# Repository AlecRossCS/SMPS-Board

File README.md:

# SMPS-Board
This is a Switch Mode Power Supply Board based on the LM2576, with output capibilities of 3.3-36V, 3A. 

### Design
this is designed to be an independent board to be the main power supply for most projects, it does not take mains input, input is meant to be either plugpack, or independent AC-DC Unit such as a Meanwell 24v, 300W supply and then transform it into 3.3V, 5V, or 12V. 

this design uses the multifaceted nature of the LM2576, as it will work with the LM2576-ADJ, LM2576-HV, LM2576-F3.3, LM2576-F5, or LM2576-F12. This meant some concern had to be taken to allow it to work either with the Adjustable or fixed versions. Some of the design rules are taken from the APP notes of the TI version datasheet. it is also designed with input protection of a PMOSFET (rather than diode protection).
It is designed to take full use of all of the copper surface of the PCB, as all of the copper is paid for to produce anyway with large planes to carry current as well as heat.

mockup:

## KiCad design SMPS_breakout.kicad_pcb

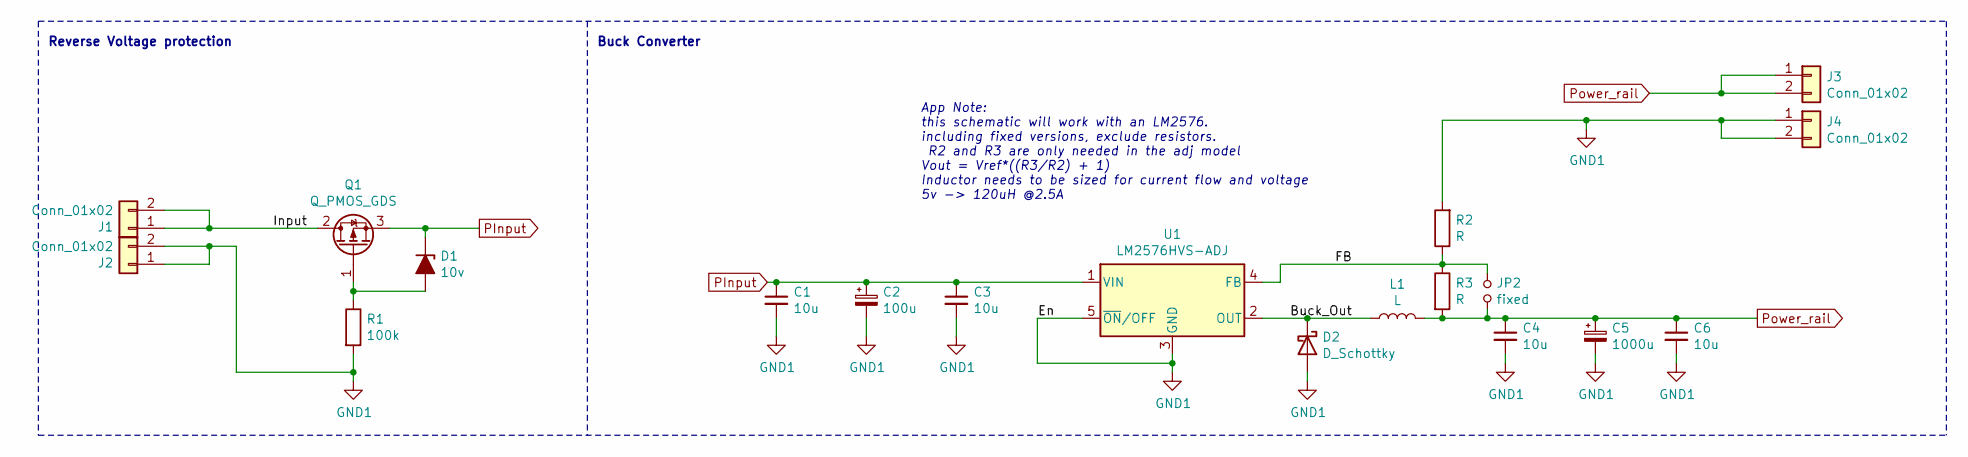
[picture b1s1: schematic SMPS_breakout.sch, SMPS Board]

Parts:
C1, C3, C4, C6: 10u; C_1210_3225Metric_Pad1.33x2.70mm_HandSolder
C2: 100u; CP_Elec_8x10
C5: 1000u; CP_Elec_16x17.5
D1: 10v; D_SOD-123
D2: D_Schottky; D_SMA-SMB_Universal_Handsoldering
J1, J2, J3, J4: Conn_01x02; PinSocket_1x02_P2.54mm_Vertical
JP2: fixed; SolderJumper-2_P1.3mm_Open_RoundedPad1.0x1.5mm
L1: L; L_Bourns_SRR1210A
Q1: Q_PMOS_GDS; TO-252-3_TabPin2
R1: 100k; R_0805_2012Metric_Pad1.20x1.40mm_HandSolder
R2, R3: R; R_0805_2012Metric_Pad1.20x1.40mm_HandSolder
U1: LM2576HVS-ADJ; TO-263-5_TabPin3

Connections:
/Buck_Out: D2.1 (K), L1.1, U1.2 (OUT)
/FB: JP2.1, R2.1, R3.1, U1.4 (FB)
/Input: J1.1, J1.2, Q1.2 (D)
GND1: C1.2, C2.2, C3.2, C4.2, C5.2, C6.2, D2.2 (A), J2.1, J2.2, J4.1, J4.2, R1.2, R2.2, U1.3 (GND), U1.5 (~ON~/OFF)
unnamed: D1.2 (A), Q1.1 (G), R1.1
PInput: C1.1, C2.1, C3.1, D1.1 (K), Q1.3 (S), U1.1 (VIN)
Power_rail: C4.1, C5.1, C6.1, J3.1, J3.2, JP2.2, L1.2, R3.2

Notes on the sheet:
Reverse Voltage protection
Buck Converter
App Note: this schematic will work with an LM2576. including fixed versions, exclude resistors. R2 and R3 are only needed in the adj model Vout = Vref*((R3/R2) + 1) Inductor needs to be sized for current flow and voltage 5v -> 120uH @2.5A

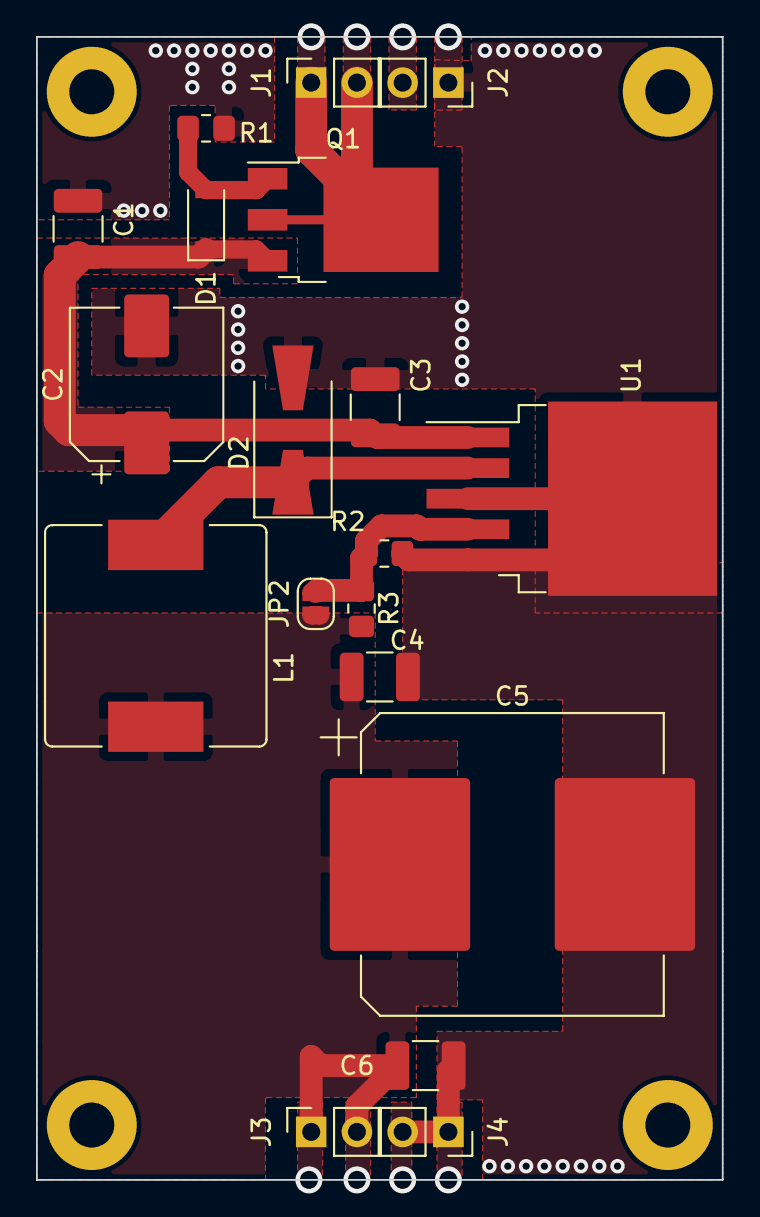
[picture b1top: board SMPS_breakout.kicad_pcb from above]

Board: 2 copper layers, 38.1 x 63.5 mm, 23 parts (0 on the bottom side), 7 nets.

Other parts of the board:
 : MountingHole_2.5mm_Pad
 #2,  #3,  #4: MountingHole_2.5mm_Pad

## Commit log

2021-10-05 Design files
    design files, will add schematics
